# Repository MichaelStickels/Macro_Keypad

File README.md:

# Macro_Keypad

Low-cost Arduino-based fully customizable 8 key macro keypad with relegendable keycaps. 

<div align="center">
  <kbd>
    
  </kbd>
</div>

## Description

This small 4x2 macro keypad offers 8 fully customizeable keys at easy reach for productivity, creative work, gaming, or other use cases. Set each key to any combination of button presses and add your own icons to the relegendable keycaps to have any shortcut, macro, or keybind ready at the push of a button. The custom PCB provides a rigid deck for the keys, as well as n-key rollover and LED backlighting. The 3D printed case angles the keys towards you for ease of use and rubber feet for grip on a slick desk.

### Features

- Low-cost, especially compared to similar products on the market ([Elgato Stream Deck](https://www.elgato.com/en/stream-deck)).
- Easily customizeable: Design your own icons for the keycaps and set each key to any combination of button presses you want in the Arduino file.
- LED backlight ready.
- Open source and fully customizeable.

### Parts

- Arduino Pro Micro (or knockoff) [[link](https://www.sparkfun.com/products/12640)]
- Cherry MX Switches [[link](https://www.digikey.com/en/products/detail/cherry-americas-llc/MX1A-11NW/91134)]
- Relegendable Keycaps [[link](https://www.amazon.com/dp/B01M023NFK?psc=1)]
- Some Headers and Jumper Cables/Wires
- 10kΩ Pullup Resistors
- 1N4148 Diodes (or similar)

I used some heat-set threaded inserts, but if you wanted to cut cost you could just screw directly into the plastic case or even just use some hot glue to secure the PCB.

### Disclaimer

Most of my projects are ongoing or work-in-progress. They are not intended to be finalized production-ready products, and should not be treated as such. Feel free to use any of the materials in this project to make your own or adapt to your own project, within the guidelines of the license.

## Getting started

### Prerequisites

Any Arduino can be used, as long as it is capable of acting as a HID (Human Interface Device). To find out if your Arduino supports it, simply google '[Arduino Name] HID keyboard'.

**Note:** The case design may need modifying to fit a different or larger board.
<!--
### Install

Ideally, write a script whose usage is described here.

### Configure

Manual, context-specific tasks not covered in the installation process.

### Usage

GIFs are useful here to see the project in action.

### Troubleshooting

Or FAQs, if that's more appropriate.
-->
## Photos

Some more photos of the project and the build process.

<div align="center">
  <kbd>
    
  </kbd>
    
  Micro USB connection on the back (from Arduino Pro Micro) and some rubber feet to prevent sliding.
</div>

<div align="center">
  <kbd>
    
  </kbd>
    
  Arduino hot-glued into the case and short jumper cables for PCB connections. I chose to use threaded heat-set inserts for the mount, but you could just as easily screw directly into the plastic.
</div>

<div align="center">
  <kbd>
    
  </kbd>
    
  Custom PCB layout and labels.
</div>

<!--
### Legal disclaimer

Usage of this tool for attacking targets without prior mutual consent is illegal. It is the end user's responsibility to obey all applicable local, state, and federal laws. Developers assume no liability and are not responsible for any misuse or damage caused by this program.
-->
<!--
### See also

- [A simple README.md template](https://gist.github.com/DomPizzie/7a5ff55ffa9081f2de27c315f5018afc)
- [A template to make good README.md](https://gist.github.com/PurpleBooth/109311bb0361f32d87a2)
- [A sample README for all your GitHub projects](https://gist.github.com/fvcproductions/1bfc2d4aecb01a834b46)
- [A simple README.md template to kickstart projects](https://github.com/me-and-company/readme-template)

## To-do

- [ ] Still need to do this
- [ ] ~~Decided not to do this~~
- [x] Done!
-->

## License

This project is licensed under the [GPL-3.0 License](LICENSE).

## Acknowledgments

* [Project inspiration from Parts Not Included](https://www.partsnotincluded.com/diy-stream-deck-mini-macro-keyboard/)
* [Keypad_Matrix Library by nickgammon](https://github.com/nickgammon/Keypad_Matrix)

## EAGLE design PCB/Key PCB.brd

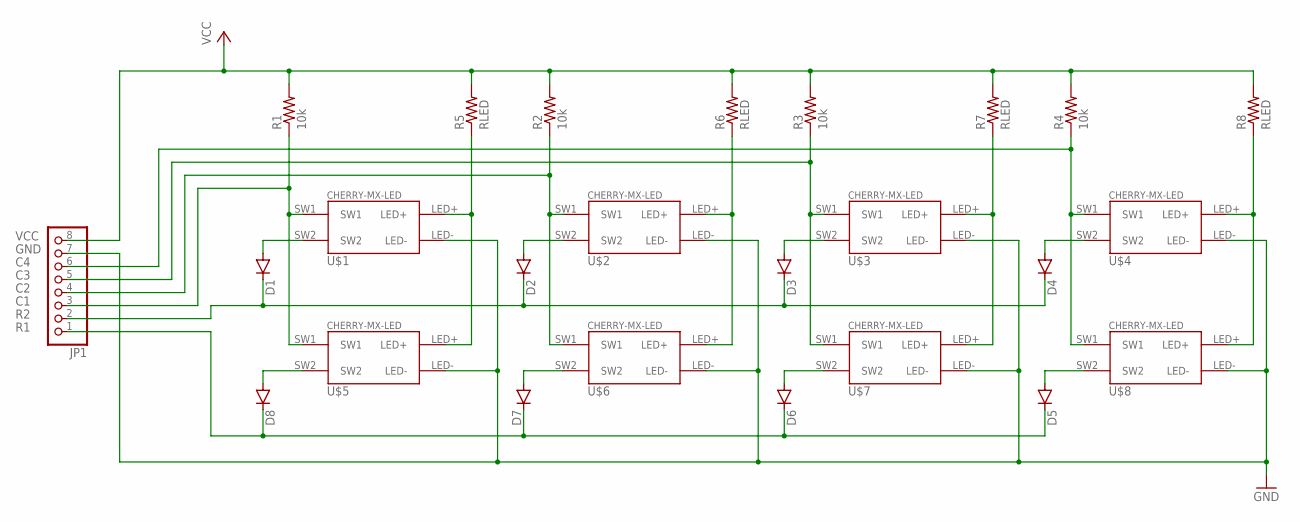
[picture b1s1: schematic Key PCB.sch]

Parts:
D1, D2, D3, D4, D5, D6, D7, D8: 1N4148DO35-7; DO35-7
JP1: PINHD-1X8; 1X08
R1, R2, R3, R4: 10k; 0207/10
R5, R6, R7, R8: RLED; 0207/10
U$1, U$2, U$3, U$4, U$5, U$6, U$7, U$8: CHERRY-MX-LED

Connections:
C1: JP1.3, R1.1, U$1.SW1, U$5.SW1
C2: JP1.4, R2.1, U$2.SW1, U$6.SW1
C3: JP1.5, R3.1, U$3.SW1, U$7.SW1
C4: JP1.6, R4.1, U$4.SW1, U$8.SW1
GND: JP1.7, U$1.LED-, U$2.LED-, U$3.LED-, U$4.LED-, U$5.LED-, U$6.LED-, U$7.LED-, U$8.LED-
unnamed: D4.A, U$4.SW2
unnamed: D1.A, U$1.SW2
unnamed: D2.A, U$2.SW2
unnamed: D3.A, U$3.SW2
unnamed: D6.A, U$7.SW2
unnamed: D7.A, U$6.SW2
unnamed: D8.A, U$5.SW2
unnamed: D5.A, U$8.SW2
unnamed: R5.1, U$1.LED+, U$5.LED+
unnamed: R6.1, U$2.LED+, U$6.LED+
unnamed: R7.1, U$3.LED+, U$7.LED+
unnamed: R8.1, U$4.LED+, U$8.LED+
R1: D5.C, D6.C, D7.C, D8.C, JP1.1
R2: D1.C, D2.C, D3.C, D4.C, JP1.2
VCC: JP1.8, R1.2, R2.2, R3.2, R4.2, R5.2, R6.2, R7.2, R8.2

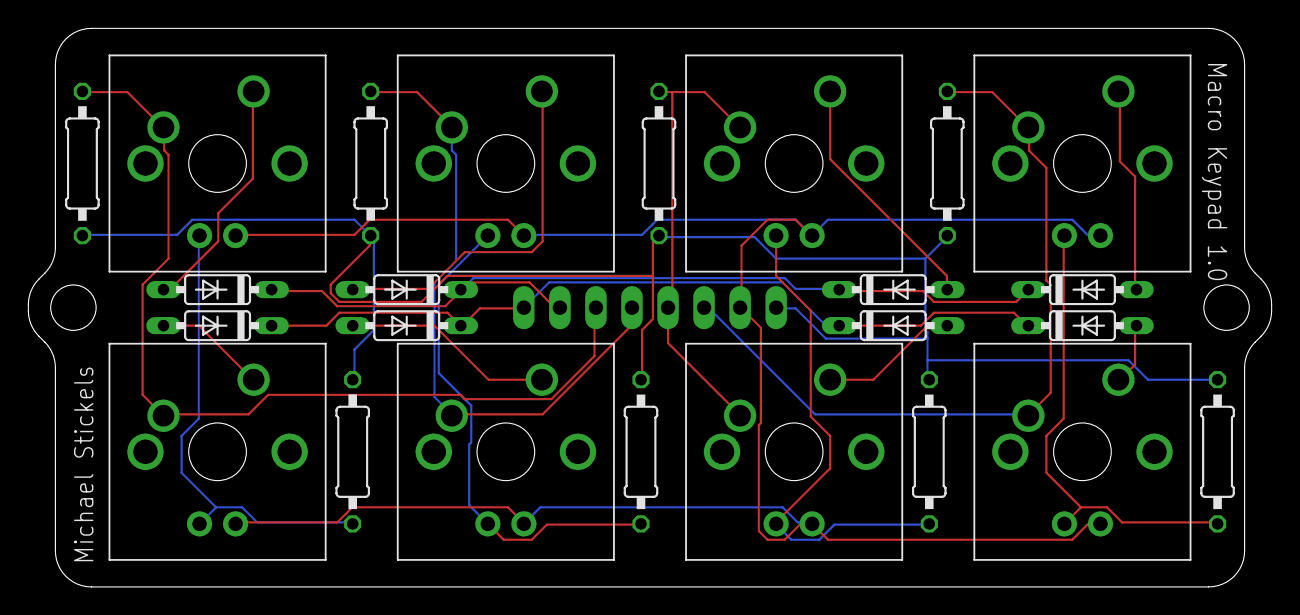
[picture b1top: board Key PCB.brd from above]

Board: 2 copper layers, 87.6 x 39.4 mm, 25 parts (0 on the bottom side), 20 nets.

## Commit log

2022-02-14 Add files
2022-02-14 Add information to README template
2022-02-14 Fix license file link in README
2022-02-14 Add customizing documentation to code
2022-02-14 Update components
2022-02-14 Change components to parts
2022-02-14 Remove unused sections
2022-03-01 Add images and disclaimer to README
2023-01-31 Add new icons
2023-02-24 Add audio switch icon
